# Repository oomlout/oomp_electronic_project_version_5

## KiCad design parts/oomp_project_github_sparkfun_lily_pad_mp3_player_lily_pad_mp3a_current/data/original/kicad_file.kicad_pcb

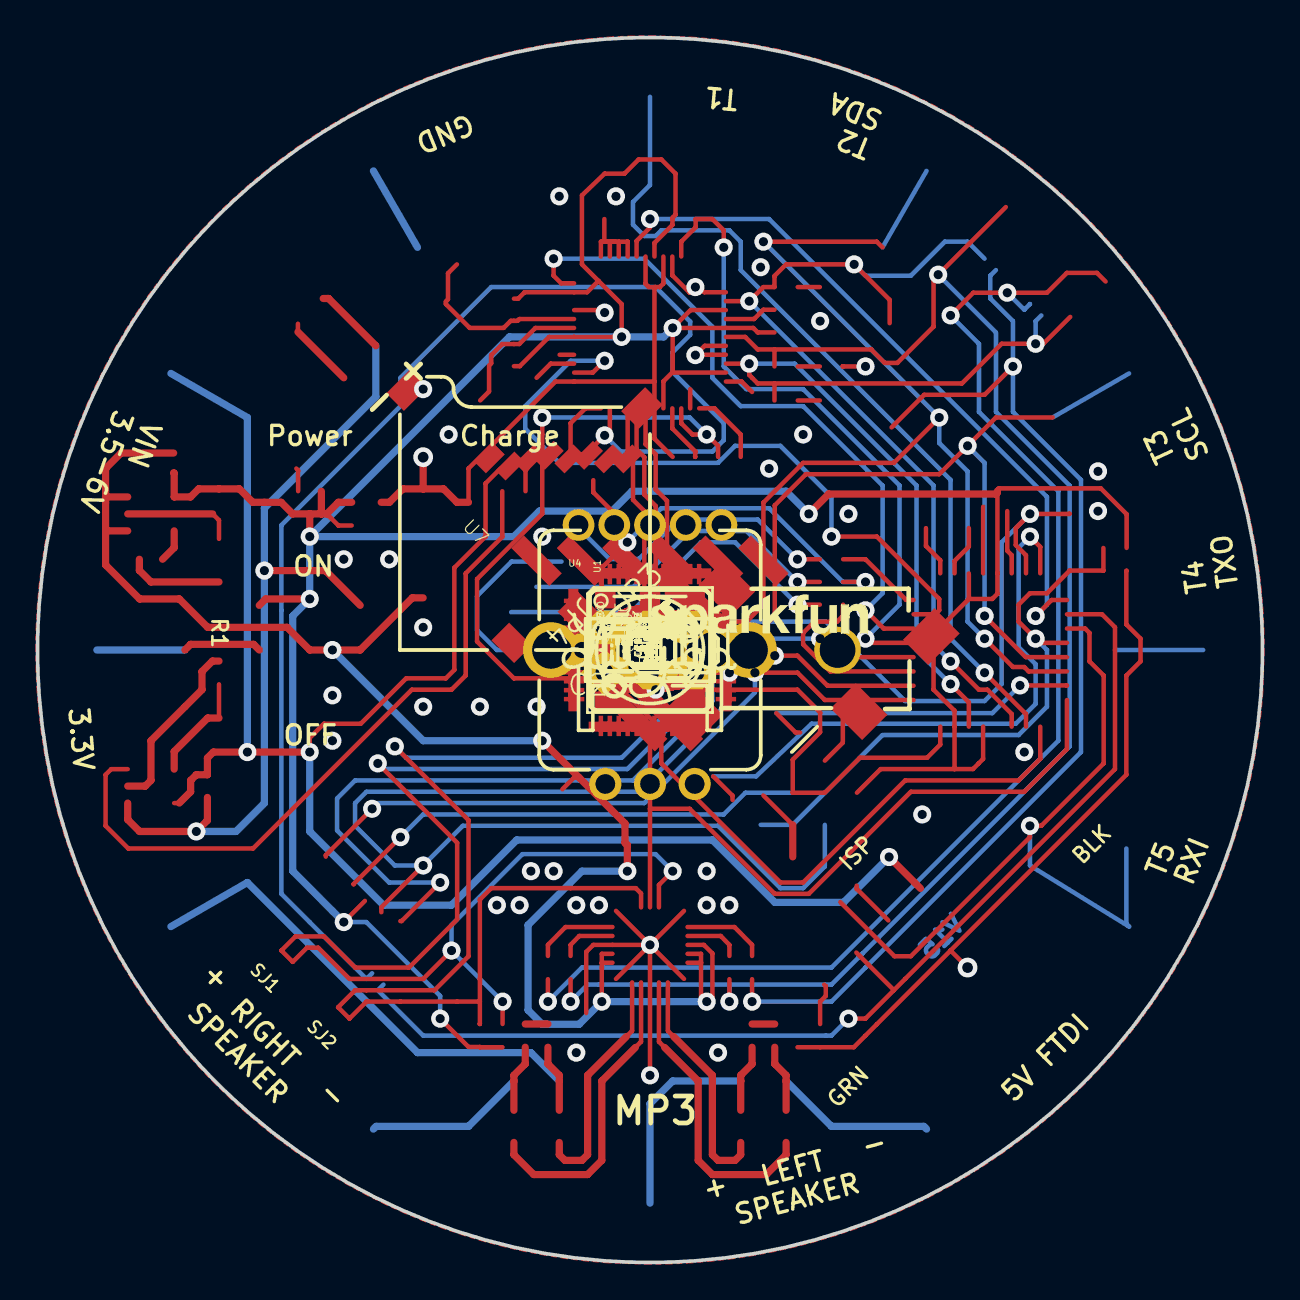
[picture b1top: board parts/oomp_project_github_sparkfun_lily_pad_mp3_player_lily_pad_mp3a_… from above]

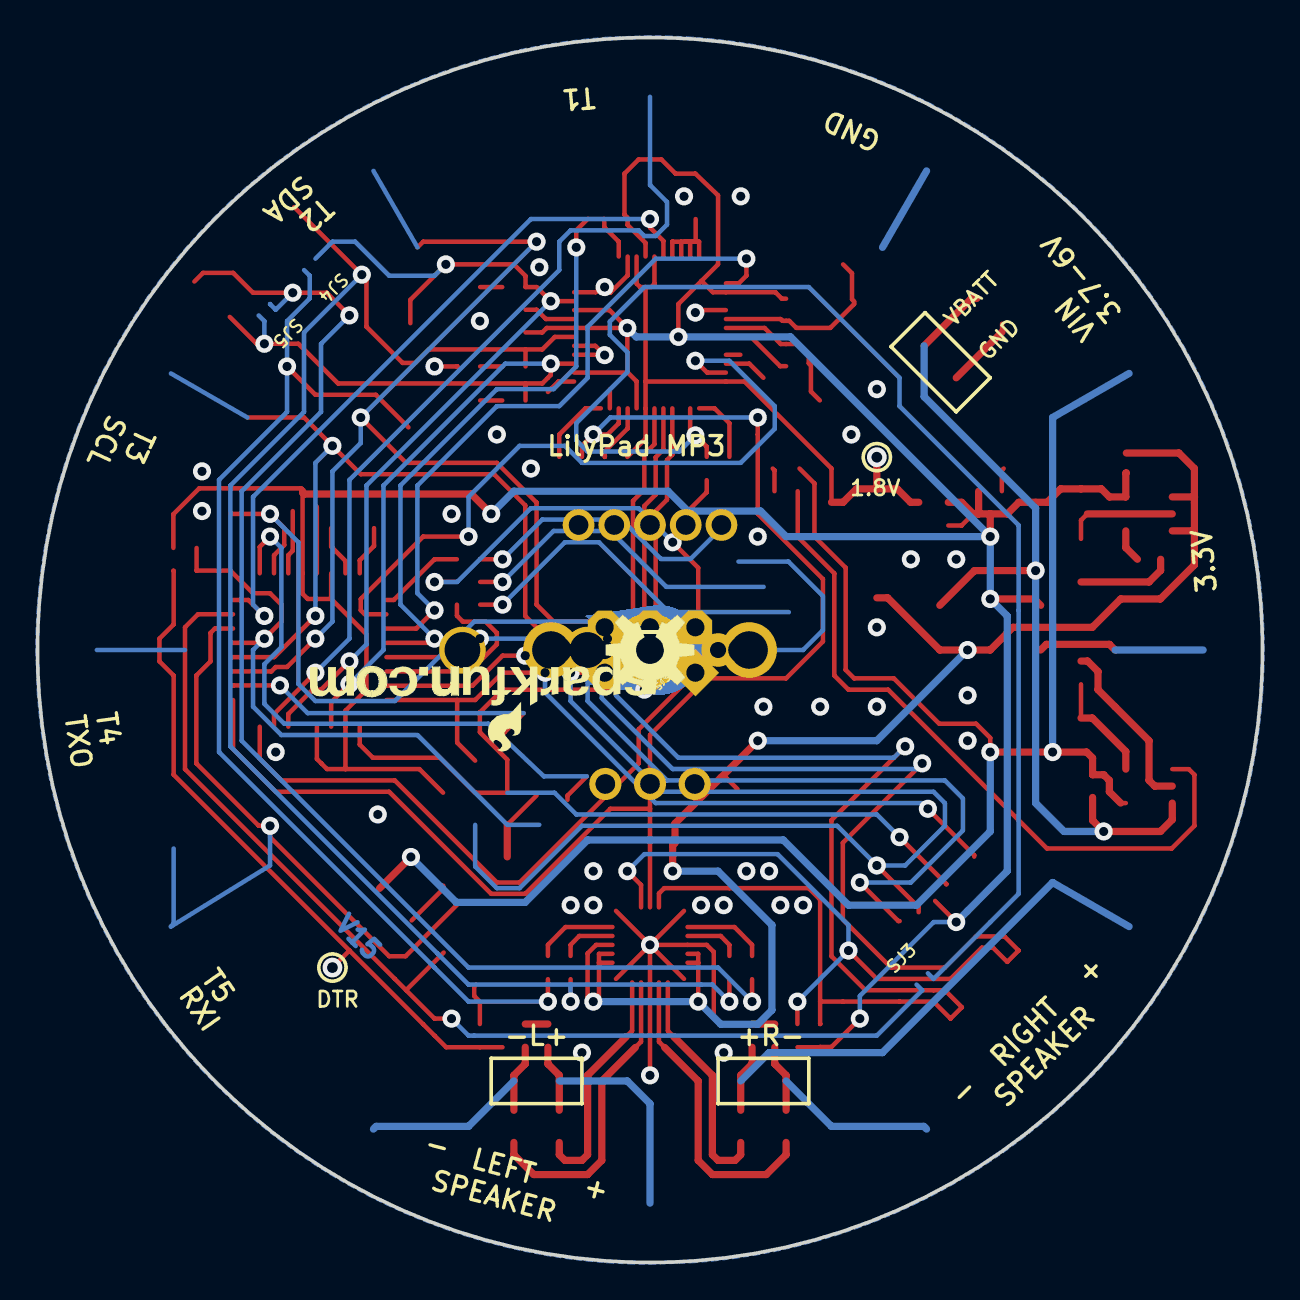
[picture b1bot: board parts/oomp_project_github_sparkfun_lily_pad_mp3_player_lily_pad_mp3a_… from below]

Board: 2 copper layers, 68.6 x 68.6 mm, 121 parts (7 on the bottom side), 69 nets.

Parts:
C1, C4, C6, C8, C18, C19, C20, C21, C23, C24, C25: 0.1uF; 0402-CAP
C2: 47uF; EIA3528
C3, C13, C26, C27, C28, C29: 1uF; 0402-CAP
C5, C7, C22: 10uF; EIA3216
C9, C10: 4.7uF; 0402-CAP
C11, C12: 22pF; 0402-CAP
C14, C15: 10nF; 0402-CAP
C16: 47nF; 0402-CAP
C17: 470pF; 0402-CAP
C30, C31, C32, C33: 1nF; 0402-CAP
D1: SOD-523
JP1: LiPo; JST-2-SMD
JP2: FTDI; 1X06-SMD
JP3: POWER; 1X02
JP4: PROG; 2X3-NS
JP5: HEADPHONE; AUDIO-JACK-3.5MM-SMD
JP6: LOGO-SFENW2; SFE-NEW-WEB
JP7, JP8: FIDUCIALUFIDUCIAL; MICRO-FIDUCIAL
L1, L2, L3, L4: 0805
LED1: RED; LED-0603
LED2: YELLOW; LED-0603
LOGO1, LOGO3: LOGO-SFESK; SFE-LOGO-FLAME
LOGO2: LOGO-SFENEW; SFE-NEW-WEBLOGO
R1, R21: 2K; 0402-RES
R1X0: DNP; AXIAL-0.3
R2, R20: 1K; 0402-RES
R3, R22: 10K; 0402-RES
R4: 1M; 0402-RES
R5, R6, R7, R13, R14, R15, R16: 100k; 0402-RES
R8, R9, R24, R25, R26: 330; 0402-RES
R10, R11: 20; 0402-RES
R12: 10; 0402-RES
R18, R19: 4.7K; 0402-RES
S1: POWER; AYZ0202
S2: EC12PLRGBSDVBF-D; ENCODER_LED_3
SJ1, SJ2, SJ3, SJ4, SJ5: SJ_2S-NO
ST1: TRIG2/SDA; PETAL-LONG-1-2SIDE
ST2: TRIG3/SCL; PETAL-LONG-1-2SIDE
ST3: TRIG4/TXO; PETAL-LONG-1-2SIDE
ST4: TRIG5/RXI; PETAL-LONG-1-2SIDE
ST5: SPKL-; PETAL-LONG-1-2SIDE
ST6: SPKL+; PETAL-LONG-1-2SIDE
ST7: SPKR-; PETAL-LONG-1-2SIDE
ST8: SPKR+; PETAL-LONG-1-2SIDE
ST9: 3.3V; PETAL-LONG-1-2SIDE
ST10: VIN; PETAL-LONG-1-2SIDE
ST11: GND; PETAL-LONG-1-2SIDE
ST12: TRIG1; PETAL-LONG-1-2SIDE
TP1: TRIG1; 1X01NS
TP2: TRIG2/SDA; 1X01NS
TP3: TRIG3/SCL; 1X01NS
TP4: TRIG4/TXO; 1X01NS
TP5: TRIG5/RXI; 1X01NS
TP6: SPKL-; 1X01NS
TP7: SPKL+; 1X01NS
TP8: SPKR-; 1X01NS
TP9: SPKR+; 1X01NS
TP10: 3.3V; 1X01NS
TP11: VIN; 1X01NS
TP12: GND; 1X01NS
TP13: DTR; PAD.03X.05
TP14: 1.8V; PAD.03X.05
U1: ATMEGA328; TQFP32-08
U2: MCP73831; SOT23-5
U3: MIC5219 3.3V; SOT23-5
U4: VS1053; LQFP-48
U5: SP6214 1.8V; SC70
U6: TPA2016D2RTJ; QFN-20-0.5MM
U7: USD-SOCKET; MICRO-SD-SOCKET-PP
U$1: LOGO-LPLP; LOGO-LILYPAD
U$4: OSHW-LOGOM; OSHW-LOGO-M
U$12: CREATIVE_COMMONS
Y1: 8MHz; RESONATOR-SMD
Y2: 12.288MHz; CRYSTAL-SMD-5X3

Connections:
1.8V: C7.A, C8.1, C21.1, TP14.P$1, U4.5, U4.7, U4.24, U4.31, U5.5
3.3V: C1.1, C3.1, C5.A, C6.1, C18.1, C19.1, C20.1, D1.A, JP4.2, R3.2, R5.2, R7.1, R8.2, R18.1, R19.1, S1.4, S2.5, U1.4, U1.6, U1.18, U1.20, U3.5, U4.6, U4.14, U4.19, U4.32, U4.38, U4.43, U4.45, U5.1, U5.3, U7.4
3.3V-TAP: S1.5, ST9.1, TP10.1
AMP-L: C28.1, JP5.TSH, SJ4.1
AMP-LX: C26.2, U6.1
AMP-R: C26.1, JP5.RSH, SJ5.1
AMP-RX: C28.2, U6.15
DTR: C4.1, R20.1, R21.2, TP13.P$1
EN-GPIO1: R13.2, U1.25, U4.34, U6.18
FTDI-DTR: JP2.1, R20.2
FTDI-RXI: JP2.3, R22.2
G1: R6.2, U4.9, U4.10, U4.11, U4.12
G2: R15.2, U4.25
GBUF: C27.1, C29.1, JP5.SLEEVE, R12.2, U4.42
GBUFLX: C27.2, U6.2
GBUFRX: C29.2, U6.14
GND: C1.2, C2.C, C3.2, C5.C, C6.2, C7.C, C8.2, C9.2, C10.2, C11.1, C12.1, C13.1, C14.2, C15.2, C16.2, C17.2, C18.2, C19.2, C20.2, C21.2, C22.C, C23.2, C24.2, C25.2, C30.2, C31.2, C32.2, C33.2, JP1.1, JP2.5, JP2.6, JP3.1, JP4.6, LED1.C, R1.2, R1X0.P$2, R2.1, R6.1, R13.1, R14.1, R15.1, R16.1, R21.1, S2.C, ST11.1, TP12.1, U1.3, U1.5, U1.21, U2.2, U3.2, U4.4, U4.16, U4.20, U4.21, U4.22, U4.35, U4.37, U4.40, U4.41, U4.47, U5.2, U6.3, U6.8, U6.PAD, U7.6, U7.CD1, U7.CD2, U7.GND1, U7.GND3, Y1.2
GPIO0: R14.2, U4.33
LEFT: JP5.TIP, R10.2, SJ4.2, U1.22, U4.46
MISO: JP4.1, U1.16, U4.30, U7.7
MOSI: JP4.4, U1.15, U4.29, U7.3
MP3-CS: U1.10, U4.23
MP3-DCS: U1.11, U4.13
MP3-DREQ: U1.32, U4.8
MP3-MIDI-RX: R5.1, SJ3.1, U4.26
MP3-RST: R7.2, U1.12, U4.3
unnamed: U1.7, Y1.1
unnamed: U1.8, Y1.3
unnamed: C13.2, U4.44
unnamed: C16.1, R12.1
unnamed: LED1.A, R8.1
unnamed: C15.1, R10.1
unnamed: LED2.C, R9.2
unnamed: C11.2, R4.2, U4.18, Y2.3
unnamed: C12.2, R4.1, U4.17, Y2.1
unnamed: C14.1, R11.1
unnamed: R24.2, S2.1
unnamed: R25.2, S2.2
unnamed: R26.2, S2.4
unnamed: L1.1, U6.6
unnamed: L2.1, U6.7
unnamed: L3.1, U6.10
unnamed: L4.1, U6.9
unnamed: C17.1, U3.4
unnamed: R16.2, U4.36
PROG: R1.1, R1X0.P$1, U2.5
RIGHT: JP5.RING, R11.2, SJ5.2, U1.19, U4.39
ROT-A: C24.1, S2.A, U1.1
ROT-B: C25.1, S2.B, U1.26
ROT-LEDB: R26.1, U1.9
ROT-LEDG: R25.1, U1.24
ROT-LEDR: R24.1, U1.14
ROT-SW: R2.2, S2.3, U1.2
RST: C4.2, JP4.5, R3.1, U1.29
SCK: JP4.3, U1.17, U4.28, U7.5
SD-CS: U1.13, U7.2
SPKL+: C32.1, L3.2, ST6.1, TP7.1
SPKL-: C33.1, L4.2, ST5.1, TP6.1
SPKR+: C30.1, L1.2, ST8.1, TP9.1
SPKR-: C31.1, L2.2, ST7.1, TP8.1
STAT: R9.1, U2.1
TRIG1: ST12.1, TP1.1, U1.23
TRIG2/SDA: R18.2, SJ2.1, SJ2.2, ST1.1, TP2.1, U1.27, U6.19
TRIG3/SCL: R19.2, SJ1.1, SJ1.2, ST2.1, TP3.1, U1.28, U6.17
TRIG4/TXO: JP2.2, SJ3.2, ST3.1, TP4.1, U1.31
TRIG5/RXI: R22.1, ST4.1, TP5.1, U1.30
VBATT: C10.1, JP1.2, JP3.2, S1.1, U2.3
VBATT_SW: C2.A, C22.A, C23.1, D1.C, S1.2, U3.1, U3.3, U6.4, U6.5, U6.11, U6.12, U6.13
VIN: C9.1, JP2.4, LED2.A, ST10.1, TP11.1, U2.4

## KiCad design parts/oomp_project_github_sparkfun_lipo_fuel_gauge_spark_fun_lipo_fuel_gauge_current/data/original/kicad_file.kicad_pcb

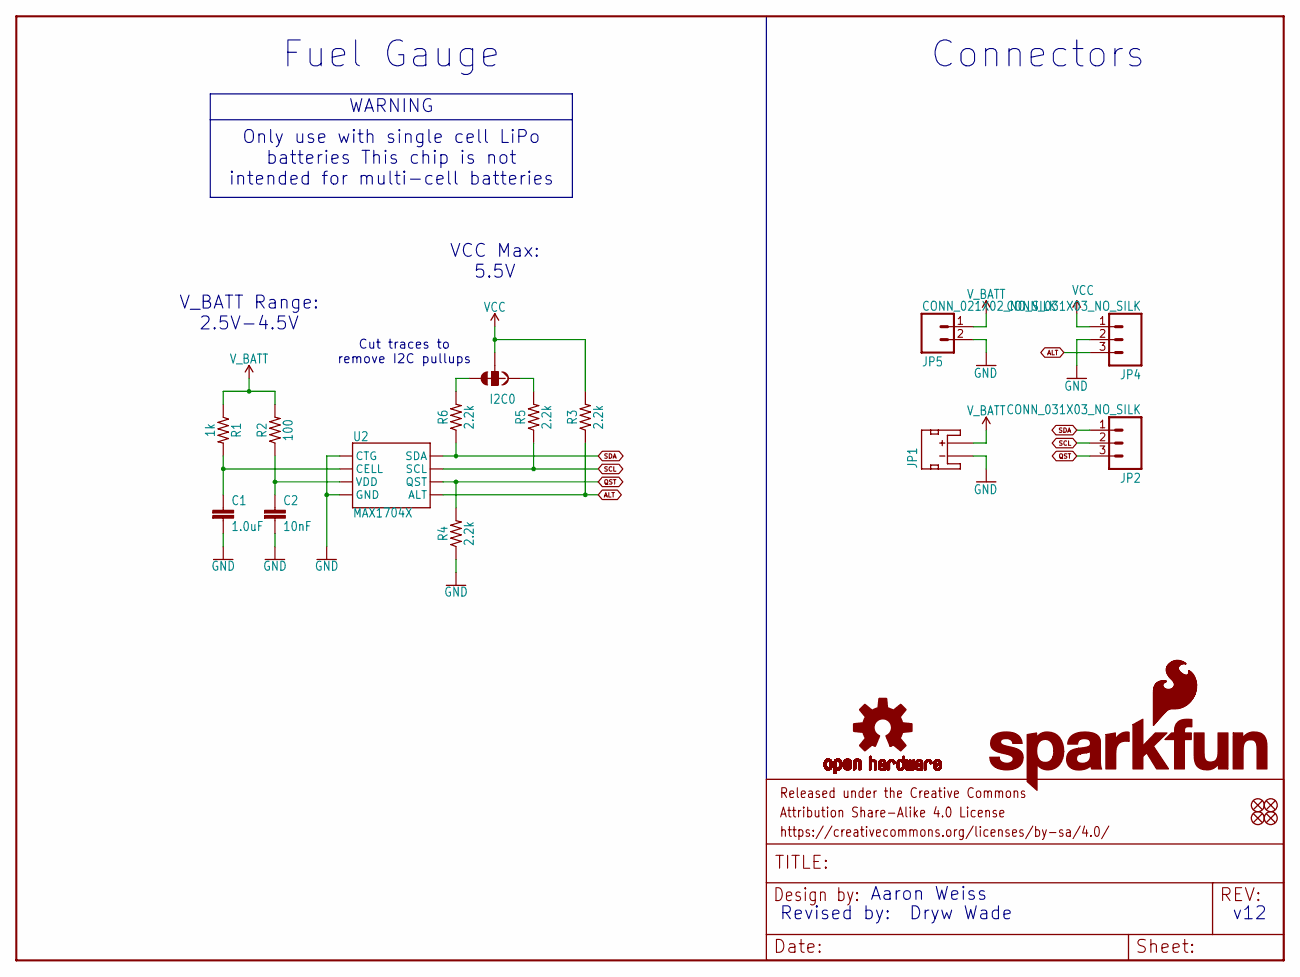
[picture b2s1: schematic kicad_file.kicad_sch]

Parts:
C1: 1.0uF; 0402-TIGHT
C2: 10nF; 0402-TIGHT
FRAME1: FRAME-LETTER; CREATIVE_COMMONS
I2C0: JUMPER-SMT_3_2-NC_TRACE_SILK; SMT-JUMPER_3_2-NC_TRACE_SILK
JP1: input; JST-2-SMD
JP2, JP4: CONN_031X03_NO_SILK; 1X03_NO_SILK
JP3: SFE_LOGO_FLAME.1_INCH; SFE_LOGO_FLAME_.1
JP5: CONN_021X02_NO_SILK; 1X02_NO_SILK
JP6, JP7, JP8, JP9: FIDUCIALUFIDUCIAL; FIDUCIAL-MICRO
LOGO1: SFE_LOGO_NAME_FLAMEBLANK; BLANK
R1: 1k; 0402-TIGHT
R2: 100; 0402-TIGHT
R3, R4, R5, R6: 2.2k; 0402-TIGHT
U2: MAX1704X; TDFN-8
U$1: OSHW-LOGOS; OSHW-LOGO-S

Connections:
ALT: JP4.3, R3.1, U2.5 (ALT)
GND: C1.2, C2.2, JP1.1 (-), JP4.2, JP5.2, R4.1, U2.1 (CTG), U2.4 (GND), U2.EP (GND)
unnamed: I2C0.3, R6.2
unnamed: C1.1, R1.2, U2.2 (CELL)
unnamed: I2C0.1, R5.2
QST: JP2.3, R4.2, U2.6 (QST)
SCL: JP2.2, R5.1, U2.7 (SCL)
SDA: JP2.1, R6.1, U2.8 (SDA)
VCC: I2C0.2, JP4.1, R3.2
VDD: C2.1, R2.1, U2.3 (VDD)
V_BATT: JP1.2 (+), JP5.1, R1.1, R2.2

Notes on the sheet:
V_BATT Range: 2.5V-4.5V
Connectors
Fuel Gauge
VCC Max: 5.5V
Aaron Weiss
Revised by:
Cut traces to remove I2C pullups
WARNING
Dryw Wade
Only use with single cell LiPo batteries~{} This chip is not intended for multi-cell batteries~{}
v12

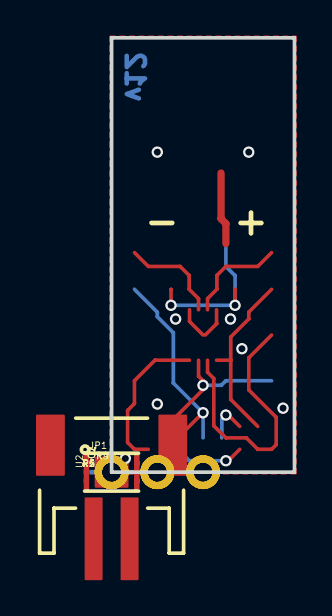
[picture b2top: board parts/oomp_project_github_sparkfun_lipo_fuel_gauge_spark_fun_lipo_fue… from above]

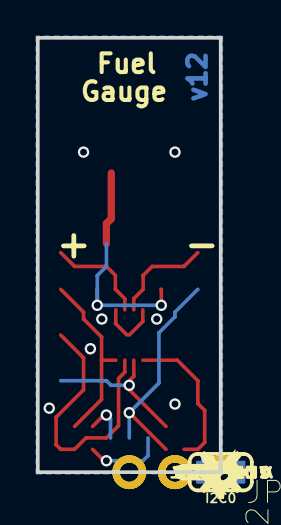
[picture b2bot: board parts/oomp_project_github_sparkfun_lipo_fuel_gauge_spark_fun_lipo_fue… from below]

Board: 2 copper layers, 10.2 x 24.1 mm, 29 parts (15 on the bottom side), 11 nets.

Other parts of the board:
U$2: SDA0
U$3: SCL0
U$4: QST0
U$5: VCC0
U$6: GND0
U$7: ALT0
U$8: #I2C#0

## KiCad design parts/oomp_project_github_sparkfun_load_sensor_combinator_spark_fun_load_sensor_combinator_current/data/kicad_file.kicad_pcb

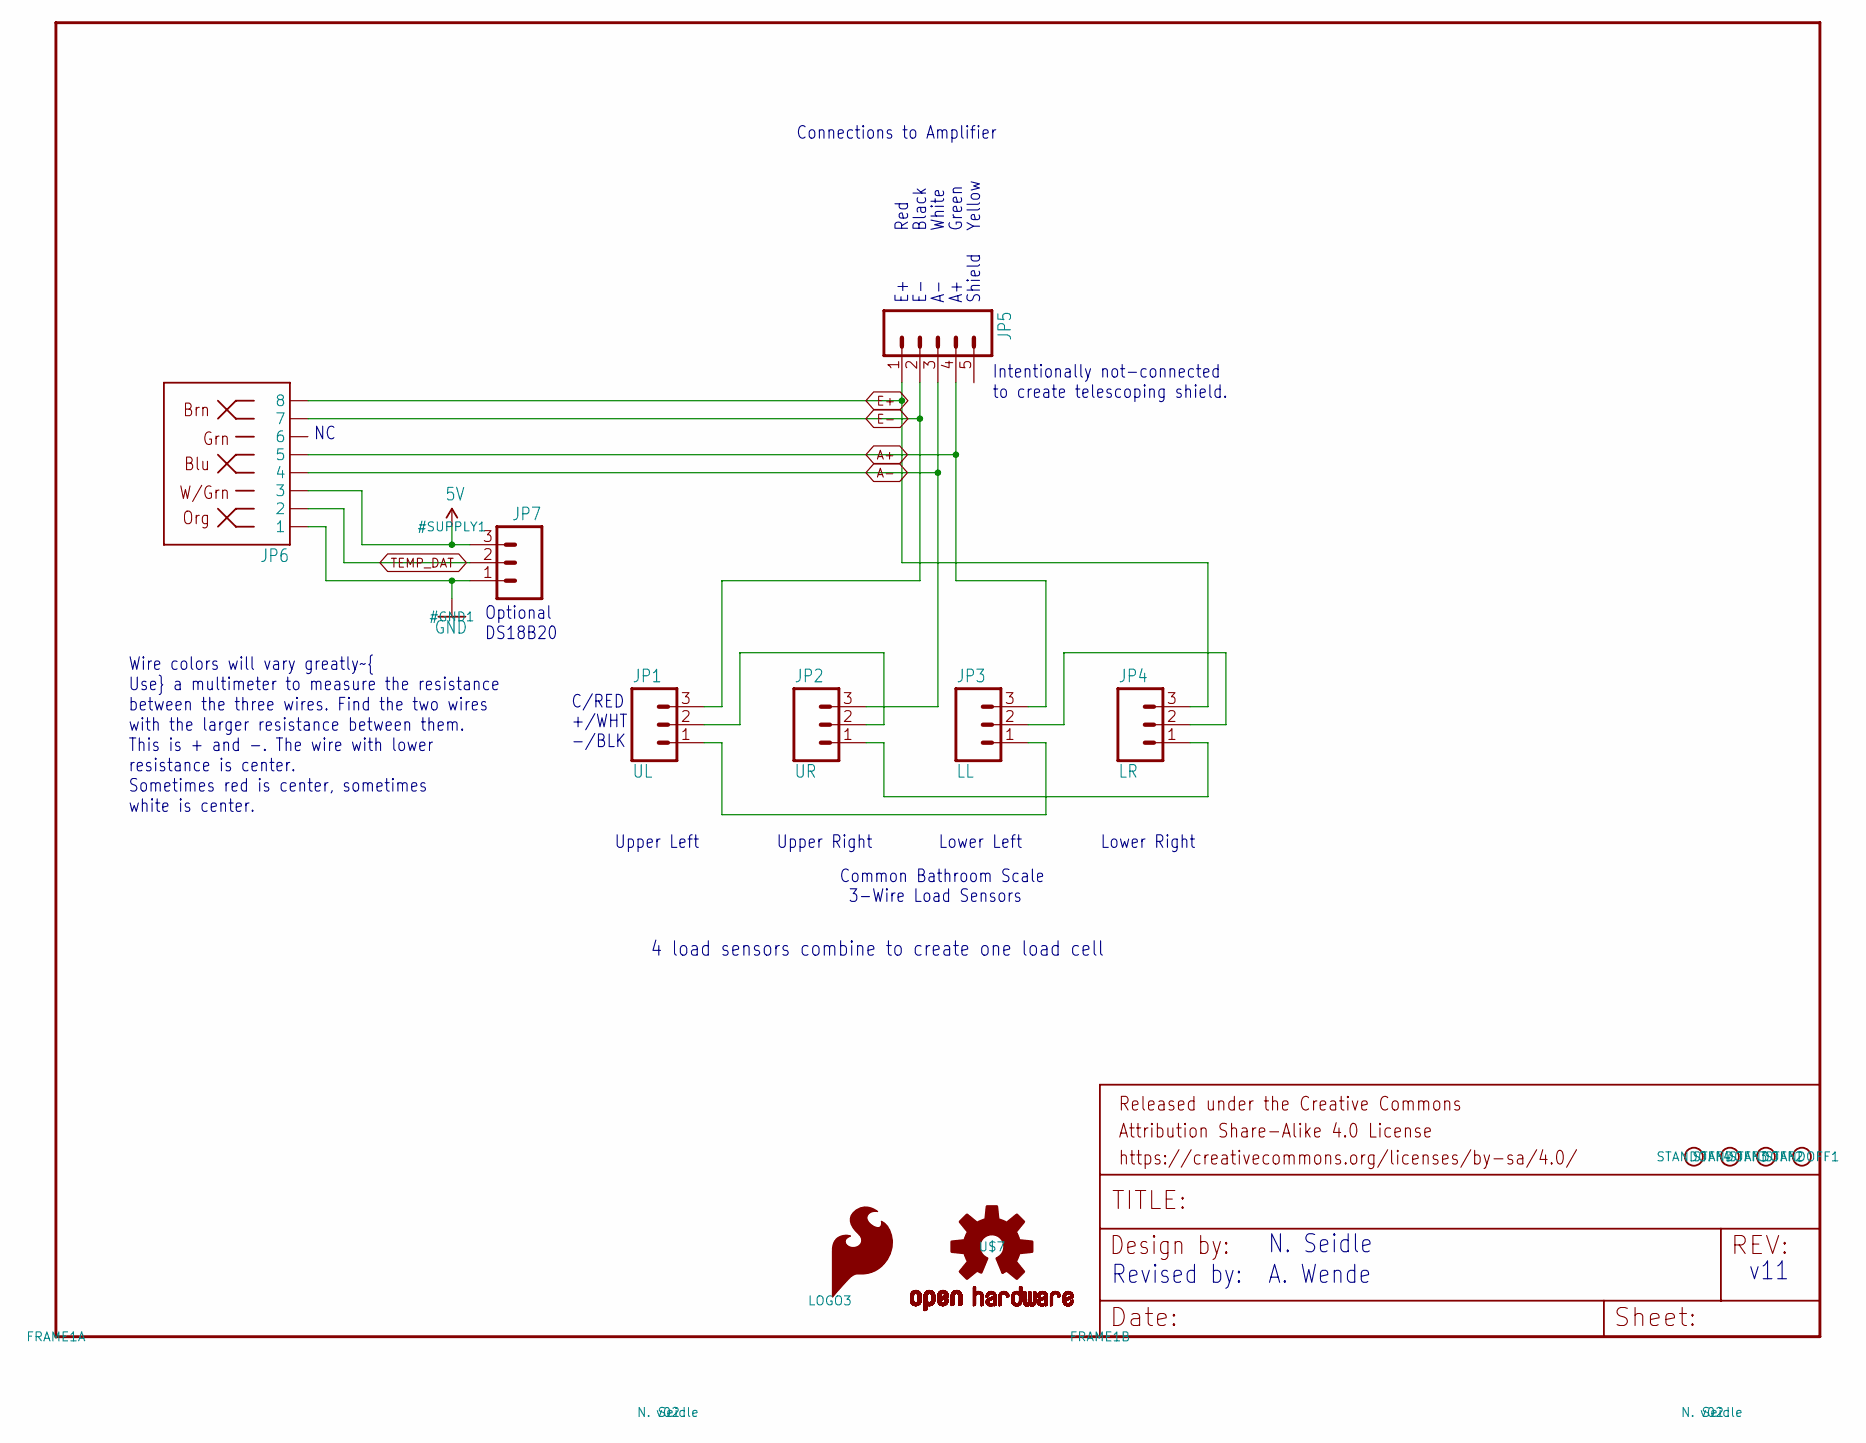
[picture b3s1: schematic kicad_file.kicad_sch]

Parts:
FRAME1: FRAME-LETTER; CREATIVE_COMMONS
JP1: UL; 1X03
JP2: UR; 1X03
JP3: LL; 1X03
JP4: LR; 1X03
JP5: M05PTH; 1X05
JP6: RJ45; RJ45-8
JP7: M03PTH; 1X03
LOGO3: SFE_LOGO_FLAME.1_INCH; SFE_LOGO_FLAME_.1
STANDOFF1, STANDOFF2, STANDOFF3, STANDOFF4: STAND-OFF
U$7: OSHW-LOGOS; OSHW-LOGO-S

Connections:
5V: JP6.3, JP7.3
A+: JP3.3, JP5.4, JP6.5
A-: JP2.3, JP5.3, JP6.4
E+: JP4.3, JP5.1, JP6.8
E-: JP1.3, JP5.2, JP6.7
GND: JP6.1, JP7.1
unnamed: JP2.1, JP4.1
unnamed: JP1.1, JP3.1
unnamed: JP3.2, JP4.2
unnamed: JP1.2, JP2.2
TEMP_DAT: JP6.2, JP7.2

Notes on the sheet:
Wire colors will vary greatly~{ Use} a multimeter to measure the resistance between the three wires. Find the two wires with the larger resistance between them. This is + and -. The wire with lower resistance is center. Sometimes red is center, sometimes white is center.
Green
Lower Left
White
4 load sensors combine to create one load cell
Yellow
Lower Right
C/RED
Revised by:
Optional DS18B20
Upper Left
Shield
+/WHT
Connections to Amplifier
Black
3-Wire Load Sensors
Red
Intentionally not-connected to create telescoping shield.
-/BLK
v11
Upper Right
A. Wende
Common Bathroom Scale
N. Seidle

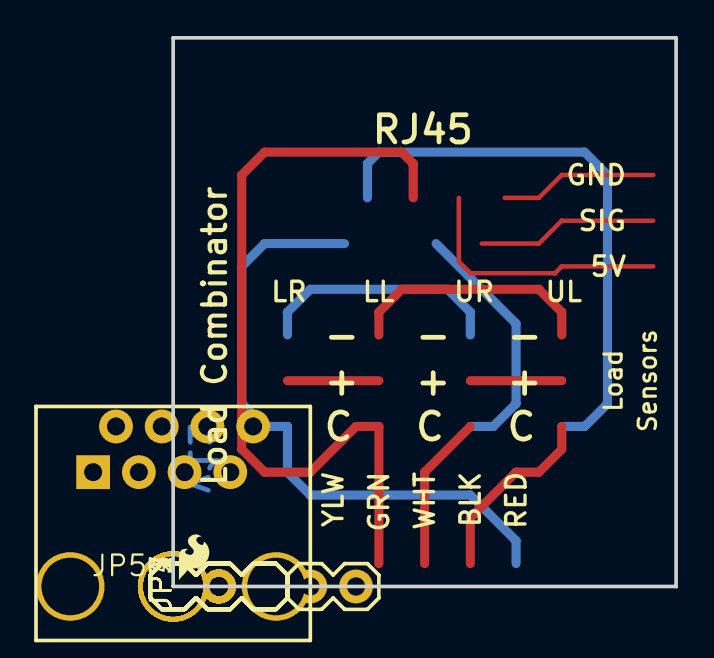
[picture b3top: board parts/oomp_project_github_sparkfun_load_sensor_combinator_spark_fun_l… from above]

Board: 2 copper layers, 27.9 x 30.5 mm, 14 parts (1 on the bottom side), 11 nets.

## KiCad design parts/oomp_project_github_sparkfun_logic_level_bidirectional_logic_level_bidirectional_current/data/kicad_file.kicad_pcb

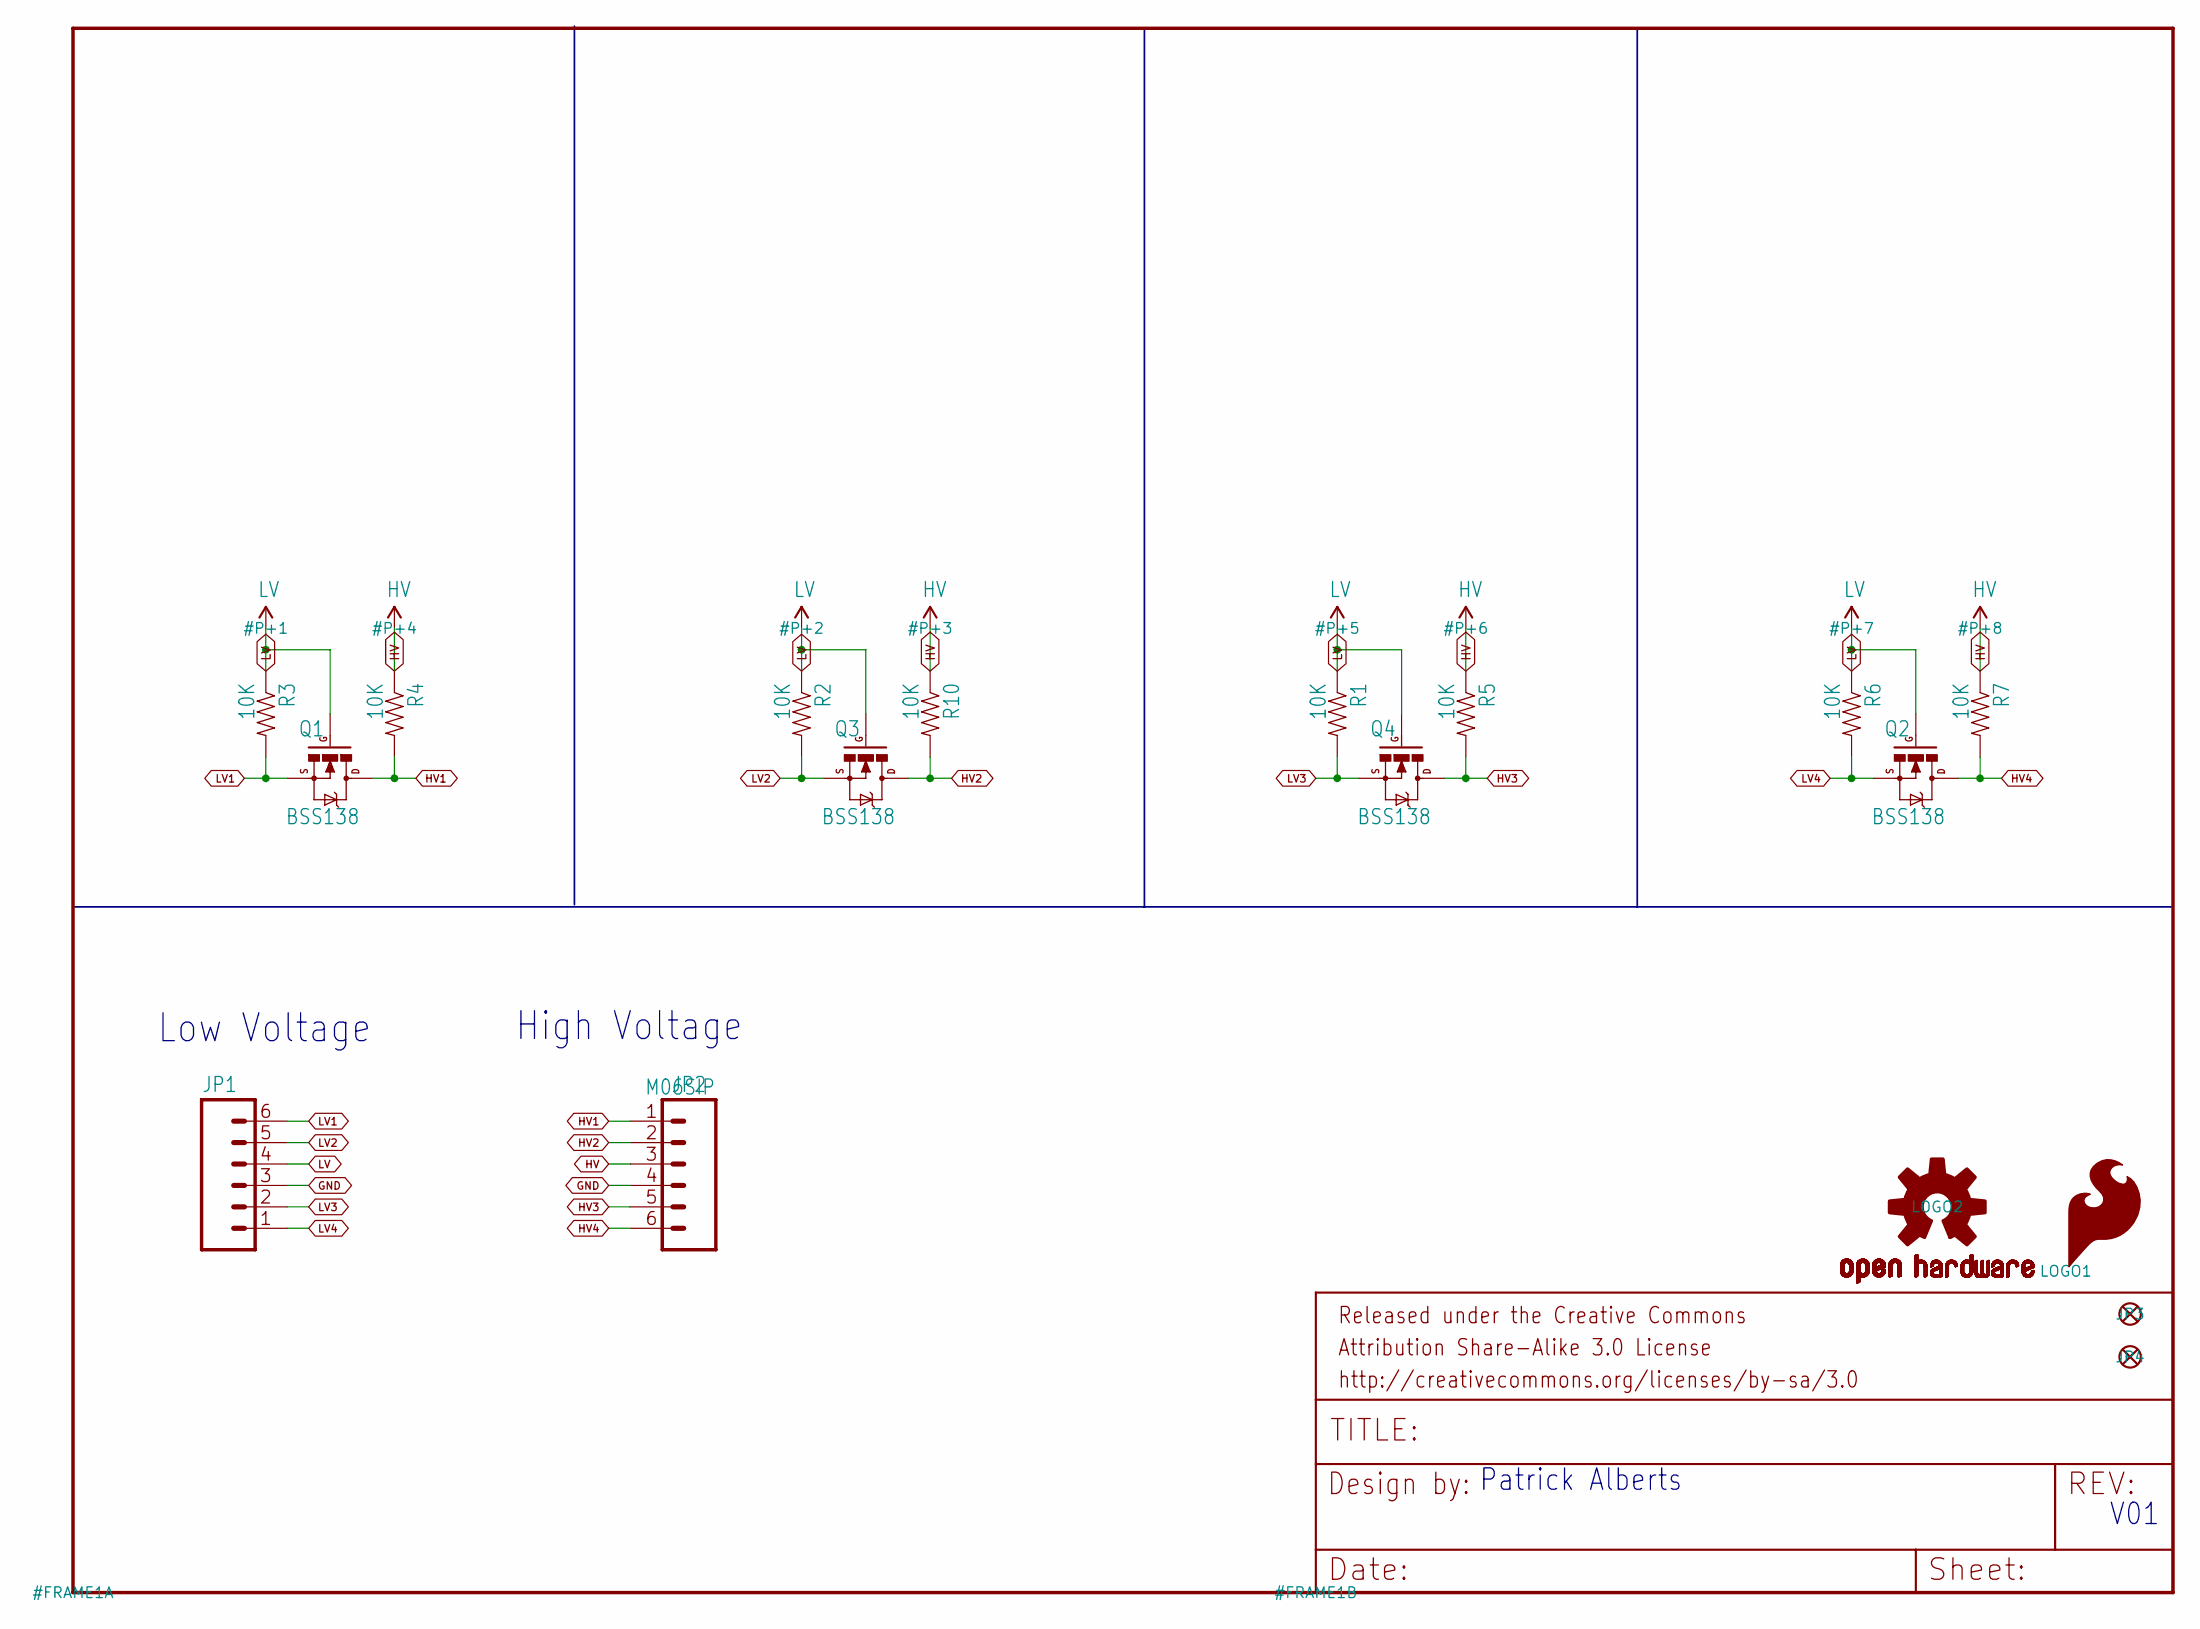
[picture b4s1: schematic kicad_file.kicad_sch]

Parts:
JP1, JP2: M06SIP; 1X06
JP3, JP4: FIDUCIALUFIDUCIAL; MICRO-FIDUCIAL
LOGO1: SFE_LOGO_FLAME.1_INCH; SFE_LOGO_FLAME_.1
LOGO2: OSHW-LOGOS; OSHW-LOGO-S
Q1, Q2, Q3, Q4: BSS138; SOT23-3
R1, R2, R3, R4, R5, R6, R7, R10: 10K; 0603-RES

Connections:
GND: JP1.3, JP2.4
HV: JP2.3, R4.1, R5.1, R7.1, R10.1
HV1: JP2.1, Q1.3 (D), R4.2
HV2: JP2.2, Q3.3 (D), R10.2
HV3: JP2.5, Q4.3 (D), R5.2
HV4: JP2.6, Q2.3 (D), R7.2
LV: JP1.4, Q1.1 (G), Q2.1 (G), Q3.1 (G), Q4.1 (G), R1.1, R2.1, R3.1, R6.1
LV1: JP1.6, Q1.2 (S), R3.2
LV2: JP1.5, Q3.2 (S), R2.2
LV3: JP1.2, Q4.2 (S), R1.2
LV4: JP1.1, Q2.2 (S), R6.2

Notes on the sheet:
V01
Low Voltage
Patrick Alberts
High Voltage

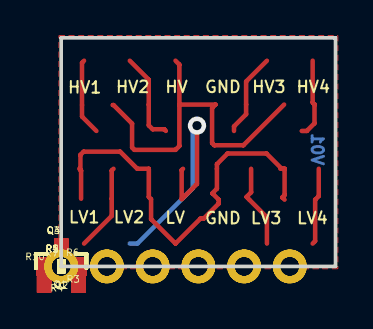
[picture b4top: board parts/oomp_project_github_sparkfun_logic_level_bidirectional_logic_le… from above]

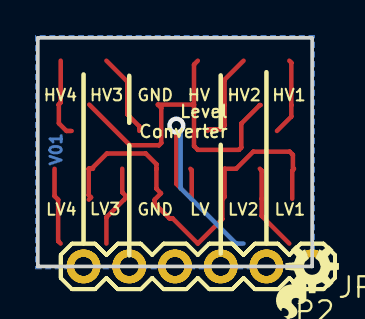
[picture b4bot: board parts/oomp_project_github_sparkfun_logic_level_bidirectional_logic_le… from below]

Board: 2 copper layers, 15.2 x 12.7 mm, 18 parts (4 on the bottom side), 11 nets.

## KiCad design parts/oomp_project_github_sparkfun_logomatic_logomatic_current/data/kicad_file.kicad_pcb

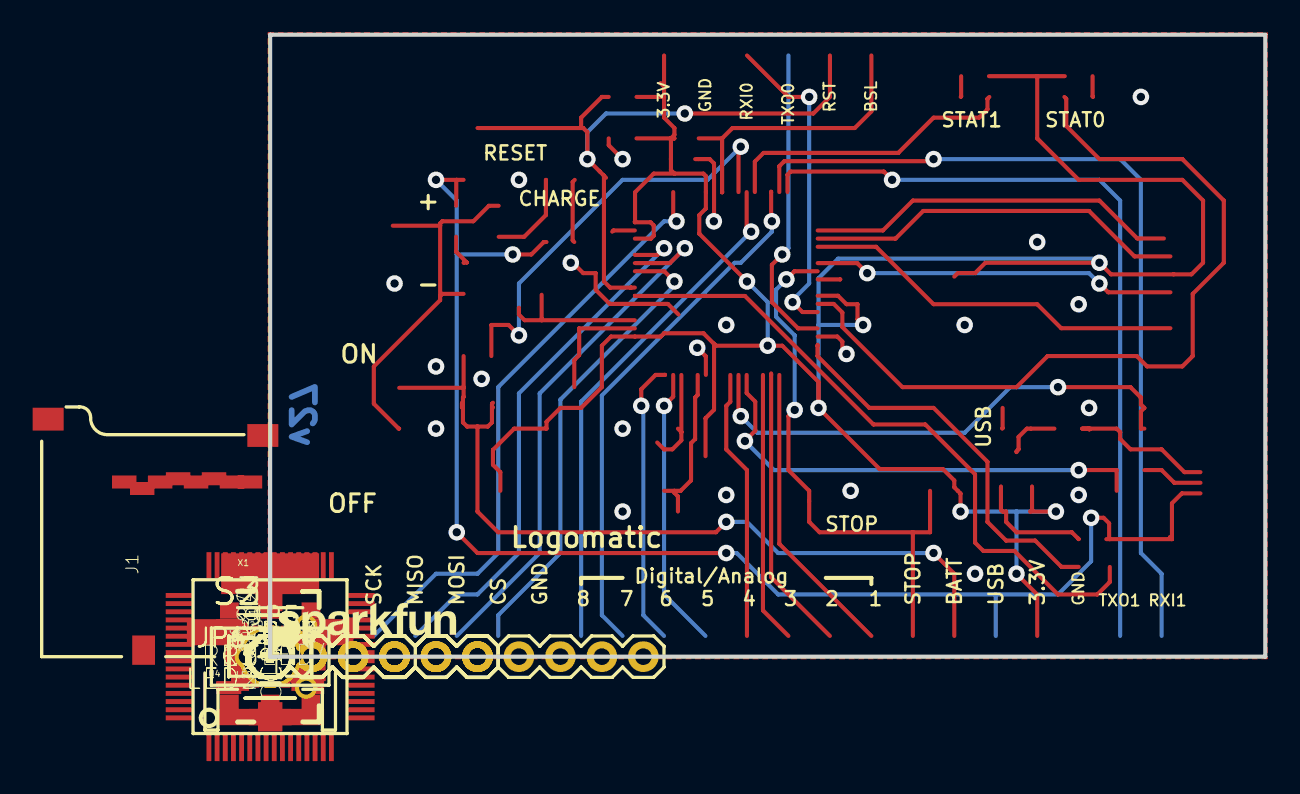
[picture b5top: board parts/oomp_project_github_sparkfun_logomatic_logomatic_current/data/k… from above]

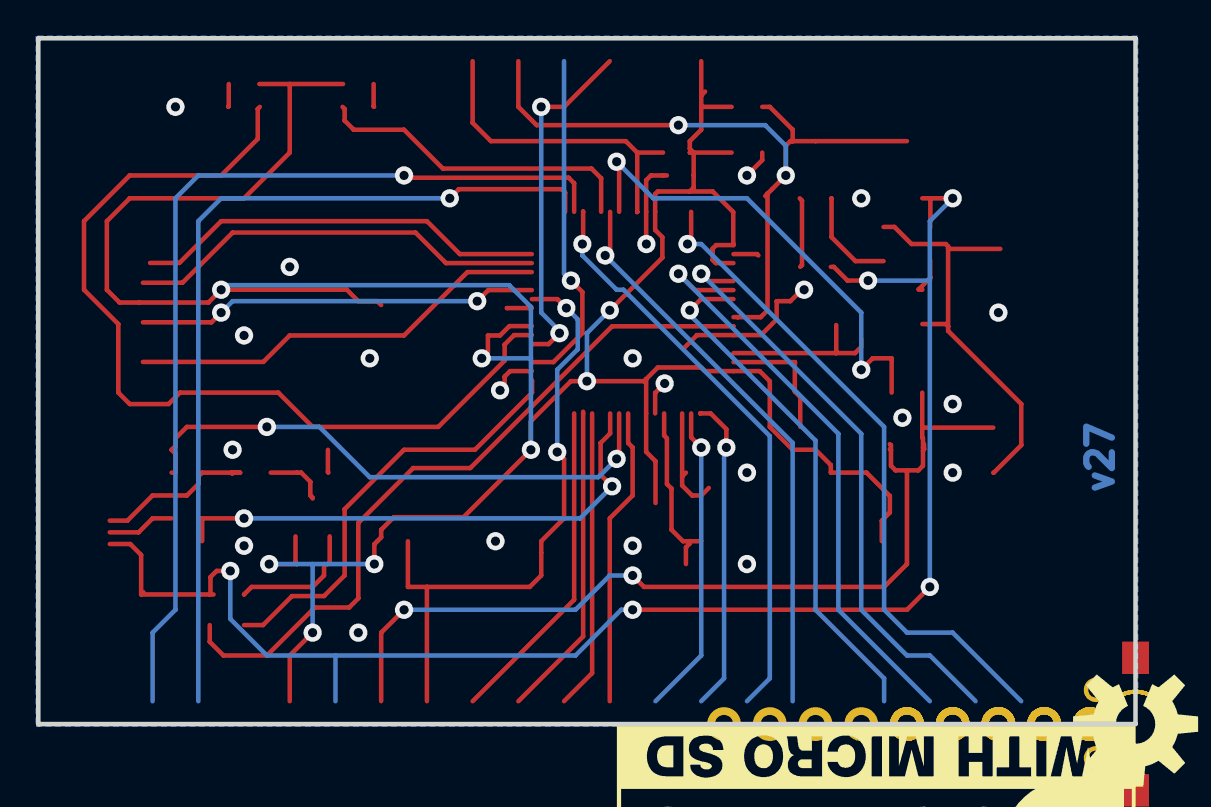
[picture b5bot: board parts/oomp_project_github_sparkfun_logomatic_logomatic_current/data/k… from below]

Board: 2 copper layers, 61.0 x 38.1 mm, 71 parts (3 on the bottom side), 52 nets.

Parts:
C1, C2, C7, C8, C9, C10, C11, C12: 0.1uF; 0603-CAP
C3, C4: 18pF; 0603-CAP
C5, C17: 4.7uF; 0603-CAP
C6: 10uF; EIA3216
C13, C14, C15, C16: 22pF; 0603-CAP
FRAME2, FRAME4: FRAME-LETTER; CREATIVE_COMMONS
J1: USD_CONNECTOR; MICRO-SD-SOCKET-PP
JP1: Prog; 1X06
JP2: LiPo; JST-2-SMD
JP4: 1X04
JP5: 1X06
JP6: M100.1; 1X10
LED1: LED RED; LED-0603
LED2: RED; LED-0603
LED3: LED-0603
LED4: GREEN; LED-0603
LOGO1: OSHW-LOGOL; OSHW-LOGO-L
LOGO2: SFE_LOGO_NAME.1_INCH; SFE_LOGO_NAME_.1
LOGO3: SFE_LOGO_FLAME.4_INCH; SFE_LOGO_FLAME_.4
Q1: 12MHz; CRYSTAL-SMD-5X3
Q2: 32kHz; CRYSTAL-32KHZ-SMD
Q4: TRANSISTOR_PNPSMD; SOT23-3
R1, R6, R7: 10K; 0603-RES@1
R2: 2.0k; 0603-RES
R3, R4, R5, R15: 330; 0603-RES
R8, R13: 10k; 0603-RES@1
R9, R10: 33; 0603-RES
R11: 1.5k; 0603
R12: 1k; 0603-RES@1
R14: 100k; 0603-RES@1
R16, R17: 1M; 0603-RES@1
R18, R19, R20: 100k; 0603-RES
S1: AYZ0202
S2: Stop; TACTILE_SWITCH_SMD
S3: Reset; TACTILE_SWITCH_SMD
U1: MCP73831; SOT23-5
U2: 3.3V; SOT23-5
U4: LPC213X; SQFP-S-10X10-64
U$1, U$2: FIDUCIAL1X2; FIDUCIAL-1X2
U$3, U$4, U$5, U$8: STAND-OFF
U$6: LOGOMATIC_LOGO
U$7: LOGO-SFESK; SFE-LOGO-FLAME
U$10: REVISION
X1: USB_MICROB_PLUGCONN-11752; USB-B-MICRO-SMD_V03

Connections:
BATTLVL: R16.2, R17.1, U4.39
BSL: JP1.1, R7.2, U4.41
CS1: JP4.1, U4.55
GND: C1.2, C2.2, C3.2, C4.2, C5.2, C6.C, C7.2, C8.2, C9.2, C10.2, C11.2, C12.2, C13.1, C14.1, C15.1, C16.1, C17.2, J1.GND, J1.GND1, J1.GND3, JP1.5, JP2.1, JP5.4, JP6.10, R2.1, R14.1, R15.1, R17.2, S2.1, S3.1, S3.2, U1.2, U2.2, U4.6, U4.18, U4.25, U4.42, U4.50, U4.59, X1.GND1
MISO0: J1.DO, U4.29
MISO1: JP4.3, U4.53
MOSI0: J1.DI, U4.30
MOSI1: JP4.2, U4.54
unnamed: R2.2, U1.5
unnamed: J1.CD1, R18.1
unnamed: J1.RSV1, R20.1
unnamed: C13.2, Q1.3, U4.62
unnamed: C16.2, Q2.X2, U4.3
unnamed: LED2.A, R4.2
unnamed: C15.2, Q2.X1, U4.5
unnamed: J1.RSV2, R19.1
unnamed: LED1.C, U1.1
unnamed: LED1.A, R3.1
unnamed: R8.1, U4.58
unnamed: Q4.1, R12.2, R13.1
unnamed: LED4.A, R5.2
unnamed: C14.2, Q1.1, U4.61
unnamed: R12.1, U4.17
unnamed: LED3.C, R15.2
P1: JP6.2, U4.15
P2: JP6.3, U4.14
P3: JP6.4, U4.13
P4: JP6.5, U4.9
P5: JP6.6, U4.2
P6: JP6.7, U4.1
P7: JP6.8, U4.35
P8: JP6.9, U4.38
P-D+: C3.1, R9.1, U4.10
P-D-: C4.1, R10.1, U4.11
RAW: JP5.1, R16.1, S1.1, U2.1, U2.3
RST: JP1.2, R1.1, S3.3, S3.4, U4.57
RXI-0: JP1.4, U4.21
RXI-1: JP5.6, U4.34
SCK0: J1.SCLK, U4.27
SCK1: JP4.4, U4.47
STAT: LED3.A, Q4.3, R11.1
STAT0: LED2.C, U4.22
STAT1: LED4.C, U4.37
STOP: C1.1, JP6.1, R6.1, S2.3, U4.26
TXO-0: JP1.3, U4.19
TXO-1: JP5.5, U4.33
USB_D+: R9.2, R11.2, X1.D+1
USB_D-: R10.2, X1.D-1
USB_VIN: C2.1, C17.1, JP5.2, R3.2, R8.2, R14.2, U1.4, X1.VBUS1
VCC: C6.A, C7.1, C8.1, C9.1, C10.1, C11.1, C12.1, J1.VCC, JP1.6, JP5.3, Q4.2, R1.2, R4.1, R5.1, R6.2, R7.1, R13.2, R18.2, R19.2, R20.2, U2.5, U4.7, U4.23, U4.43, U4.49, U4.51, U4.63
VLIPO: C5.1, JP2.2, S1.2, U1.3
~CS0: J1.CS, U4.31

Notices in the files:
parts/oomp_project_github_sparkfun_lipo_fuel_gauge_spark_fun_lipo_fuel_gauge_current/data/original/kicad_file.kicad_sch:
Released under the Creative Commons
https://creativecommons.org/licenses/by-sa/4.0
parts/oomp_project_github_sparkfun_logic_level_bidirectional_logic_level_bidirectional_current/data/kicad_file.kicad_sch:
http://creativecommons.org/licenses/by-sa/3.0
parts and their libraries:
Released under the Creative Commons Attribution Share-Alike 3.0 License
Released under the Creative Commons Attribution Share-Alike 4.0 License
